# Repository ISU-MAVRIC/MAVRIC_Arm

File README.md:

# MAVRIC_Arm
The MAVRIC Arm consists of a rotating base (stepper motor), 'shoulder' actuator (with feedback), 'elbow' actuator (with feedback), and an end effector. The end effector is modular but at its maximum contains a rotation servo, horizontal servo, vertical servo, and gripping servo. This board interfaces with the MAVRIC main board, receiving control packets and sending back status packets.

**Features**
- 4 7.4V 5A Buck Regulators powering the high power end effector servos
  - Current measurement on every power output to prevent overheating of both the regulators and the servos themselves
- 3V3 and 5V Buck Regulators powering the STM32 and an external Raspberry Pi
- Powered by single 12V battery rail
- STM32 communicating over RS-485 with the MAVRIC main board for control/status transmission
- STM32 generating PWM to control the actuator drivers, servos, and stepper driver

## Arm Board Prototype 1 Ordered:

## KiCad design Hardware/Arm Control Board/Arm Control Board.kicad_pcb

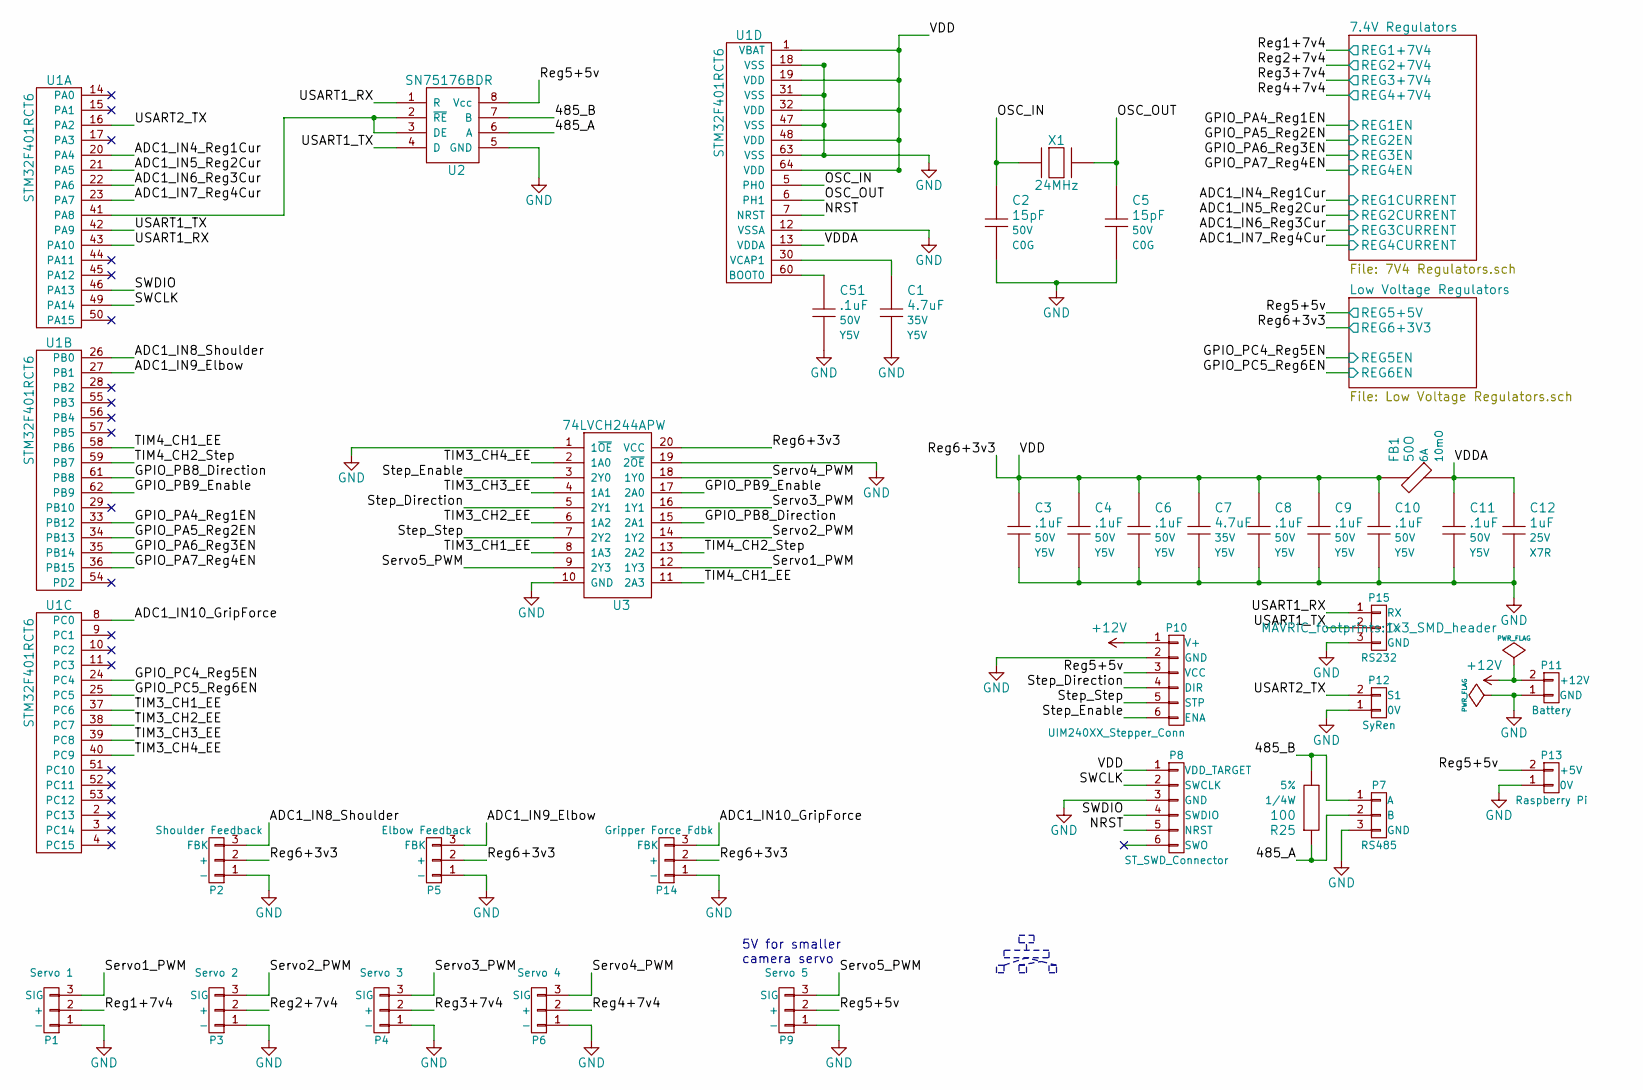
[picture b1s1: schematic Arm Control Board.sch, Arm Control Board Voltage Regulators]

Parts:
C1, C7: 4.7uF; C_1206_HandSoldering; Voltage 35V; Manufacturer Part # GMK316F475ZG-T
C2, C5: 15pF; C_1206_HandSoldering; Voltage 50V; Manufacturer Part # CL31C150JBCNNNC
C3, C4, C6, C8, C9, C10, C11, C51: .1uF; C_1206_HandSoldering; Voltage 50V; Manufacturer Part # CL31F104MBCNNNC
C12: 1uF; C_1206_HandSoldering; Voltage 25V; Manufacturer Part # C1206C105M3RACTU
FB1: 50O; R_1206_HandSoldering; Manufacturer Part # HI1206T500R-10
P1: Servo 1; 1x3_SMD_header
P2: Shoulder Feedback; 1x3_SMD_header
P3: Servo 2; 1x3_SMD_header
P4: Servo 3; 1x3_SMD_header
P5: Elbow Feedback; 1x3_SMD_header
P6: Servo 4; 1x3_SMD_header
P7: RS485; 1x3_SMD_header
P8: ST_SWD_Connector; 1x6_SMD_header
P9: Servo 5; 1x3_SMD_header
P10: UIM240XX_Stepper_Conn; 1x6_SMD_header
P11: Battery; SolderWirePad_2x_2-5mmDrill
P12: SyRen; 1x2_SMD_header
P13: Raspberry Pi; 1x2_SMD_header
P14: Gripper Force Fdbk; 1x3_SMD_header
P15: RS232; 1x3_SMD_header
R25: 100; R_1206_HandSoldering; Tolerance 5%; Manufacturer Part # ERJ-8GEYJ101V
U1: STM32F401RCT6; LQFP-64_10x10mm_Pitch0.5mm
U2: SN75176BDR; SOIC-8-W
U3: 74LVCH244APW; AB2_TSSOP20
X1: 24MHz; Q_49U3HMS; Tolerance 30ppm; Manufacturer Part # 9C-24.000MAAE-T; Digi-Key Value

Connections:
+12V: P10.1 (V+), P11.2 (+12V); also elsewhere on the board
/7.4V Regulators/REG1+7V4: P1.2 (+); also elsewhere on the board
/7.4V Regulators/REG1CURRENT: U1.20 (PA4); also elsewhere on the board
/7.4V Regulators/REG1EN: U1.33 (PB12); also elsewhere on the board
/7.4V Regulators/REG2+7V4: P3.2 (+); also elsewhere on the board
/7.4V Regulators/REG2CURRENT: U1.21 (PA5); also elsewhere on the board
/7.4V Regulators/REG2EN: U1.34 (PB13); also elsewhere on the board
/7.4V Regulators/REG3+7V4: P4.2 (+); also elsewhere on the board
/7.4V Regulators/REG3CURRENT: U1.22 (PA6); also elsewhere on the board
/7.4V Regulators/REG3EN: U1.35 (PB14); also elsewhere on the board
/7.4V Regulators/REG4+7V4: P6.2 (+); also elsewhere on the board
/7.4V Regulators/REG4CURRENT: U1.23 (PA7); also elsewhere on the board
/7.4V Regulators/REG4EN: U1.36 (PB15); also elsewhere on the board
/485_A: P7.2 (B), R25.1, U2.6 (A)
/485_B: P7.1 (A), R25.2, U2.7 (B)
/ADC1_IN8_Shoulder: P2.3 (FBK), U1.26 (PB0)
/ADC1_IN9_Elbow: P5.3 (FBK), U1.27 (PB1)
/ADC1_IN10_GripForce: P14.3 (FBK), U1.8 (PC0)
/GPIO_PB8_Direction: U1.61 (PB8), U3.15 (2A1)
/GPIO_PB9_Enable: U1.62 (PB9), U3.17 (2A0)
/Low Voltage Regulators/REG5+5V: P9.2 (+), P10.3 (VCC), P13.2 (+5V), U2.8 (Vcc); also elsewhere on the board
/Low Voltage Regulators/REG5EN: U1.24 (PC4); also elsewhere on the board
/Low Voltage Regulators/REG6+3V3: C3.1, C4.1, C6.1, C7.1, C8.1, C9.1, C10.1, FB1.1, P2.2 (+), P5.2 (+), P8.1 (VDD_TARGET), P14.2 (+), U1.1 (VBAT), U1.19 (VDD), U1.32 (VDD), U1.48 (VDD), U1.64 (VDD), U3.20 (VCC); also elsewhere on the board
/Low Voltage Regulators/REG6EN: U1.25 (PC5); also elsewhere on the board
/NRST: P8.5 (NRST), U1.7 (NRST)
/OSC_IN: C2.1, U1.5 (PH0), X1.1
/OSC_OUT: C5.1, U1.6 (PH1), X1.2
/SWCLK: P8.2 (SWCLK), U1.49 (PA14)
/SWDIO: P8.4 (SWDIO), U1.46 (PA13)
/Servo1_PWM: P1.3 (SIG), U3.12 (1Y3)
/Servo2_PWM: P3.3 (SIG), U3.14 (1Y2)
/Servo3_PWM: P4.3 (SIG), U3.16 (1Y1)
/Servo4_PWM: P6.3 (SIG), U3.18 (1Y0)
/Servo5_PWM: P9.3 (SIG), U3.9 (2Y3)
/Step_Direction: P10.4 (DIR), U3.5 (2Y1)
/Step_Enable: P10.6 (ENA), U3.3 (2Y0)
/Step_Step: P10.5 (STP), U3.7 (2Y2)
/TIM3_CH1_EE: U1.37 (PC6), U3.8 (1A3)
/TIM3_CH2_EE: U1.38 (PC7), U3.6 (1A2)
/TIM3_CH3_EE: U1.39 (PC8), U3.4 (1A1)
/TIM3_CH4_EE: U1.40 (PC9), U3.2 (1A0)
/TIM4_CH1_EE: U1.58 (PB6), U3.11 (2A3)
/TIM4_CH2_Step: U1.59 (PB7), U3.13 (2A2)
/USART1_RX: P15.1 (RX), U1.43 (PA10), U2.1 (R)
/USART1_TX: P15.2 (TX), U1.42 (PA9), U2.4 (D)
/USART2_TX: P12.2 (S1), U1.16 (PA2)
/VDDA: C11.1, C12.1, FB1.2, U1.13 (VDDA)
GND: C1.2, C2.2, C3.2, C4.2, C5.2, C6.2, C7.2, C8.2, C9.2, C10.2, C11.2, C12.2, C51.2, P1.1 (-), P2.1 (-), P3.1 (-), P4.1 (-), P5.1 (-), P6.1 (-), P7.3 (GND), P8.3 (GND), P9.1 (-), P10.2 (GND), P11.1 (GND), P12.1 (0V), P13.1 (0V), P14.1 (-), P15.3 (GND), U1.12 (VSSA), U1.18 (VSS), U1.31 (VSS), U1.47 (VSS), U1.63 (VSS), U2.5 (GND), U3.1 (1~OE), U3.10 (GND), U3.19 (2~OE); also elsewhere on the board
unnamed: C1.1, U1.30 (VCAP1)
unnamed: C51.1, U1.60 (BOOT0)
unnamed: U1.41 (PA8), U2.2 (~RE), U2.3 (DE)

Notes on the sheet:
5V for smaller camera servo

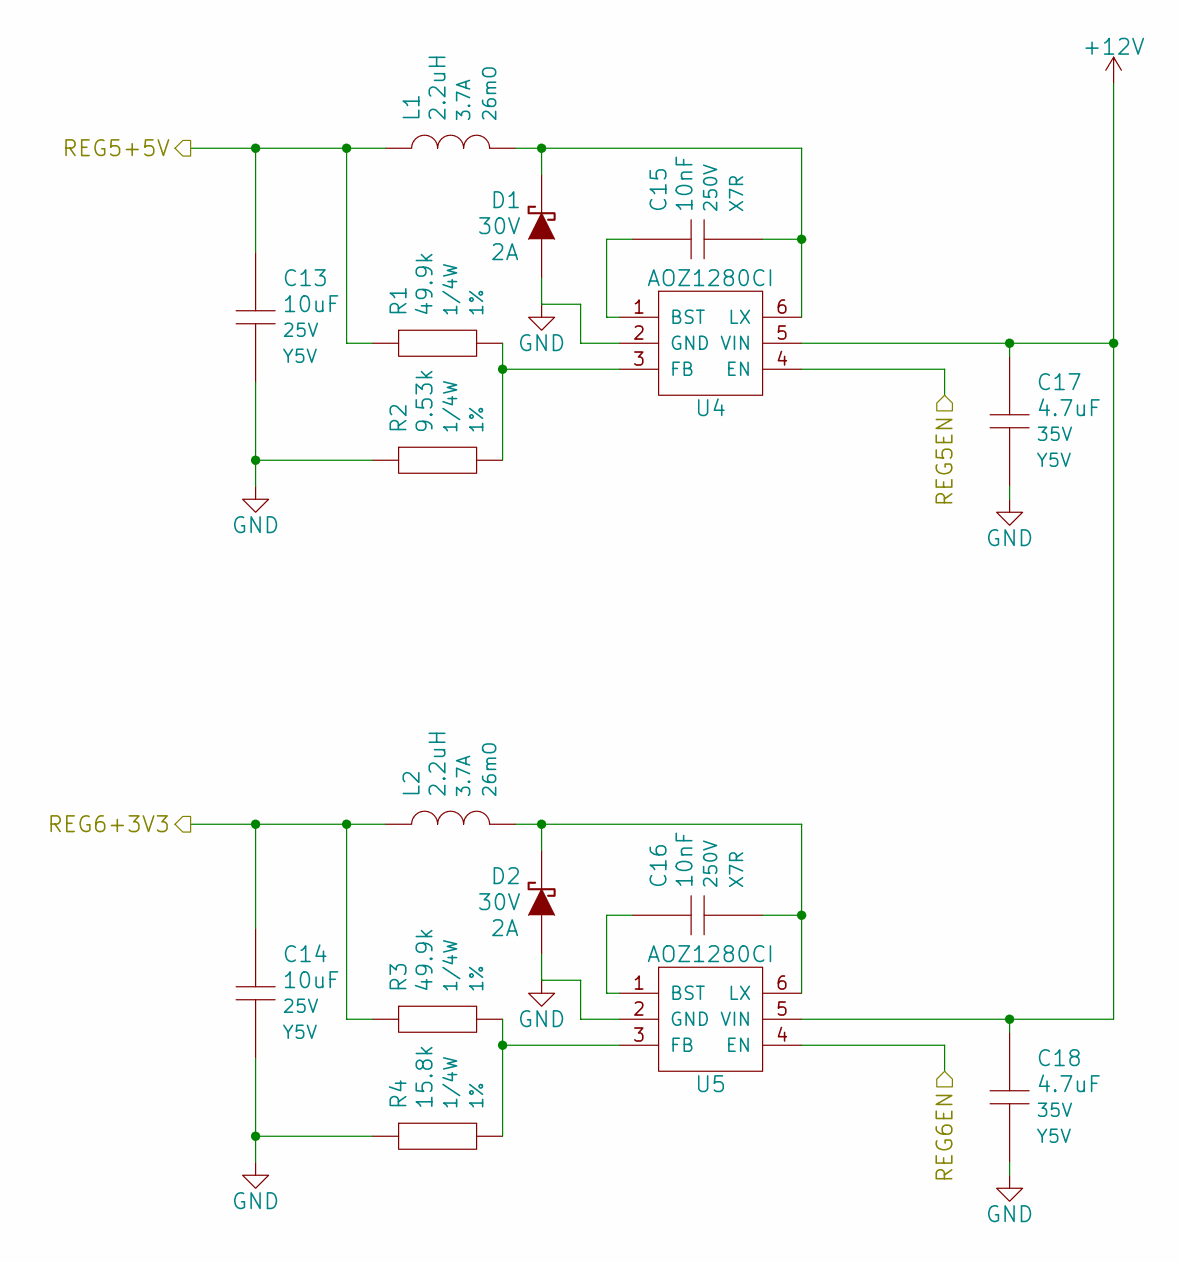
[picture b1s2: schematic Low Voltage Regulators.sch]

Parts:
C13, C14: 10uF; C_1206_HandSoldering; Voltage 25V; Manufacturer Part # TMK316F106ZL-T
C15, C16: 10nF; C_1206_HandSoldering; Voltage 250V; Manufacturer Part # C1206C103JARACTU; Digi-Key Value
C17, C18: 4.7uF; C_1206_HandSoldering; Voltage 35V; Manufacturer Part # GMK316F475ZG-T
D1, D2: DIODESCH; Diode_MicroSMP; Reverse Voltage 30V; Manufacturer Part # MSS2P3-M3/89A
L1, L2: 2.2uH; Yuden_SMD_Power_Inductor_6060; Manufacturer Part # NR6028T2R2N
R1, R3: 49.9k; R_1206_HandSoldering; Tolerance 1%; Manufacturer Part # RC1206FR-0749K9L
R2: 9.53k; R_1206_HandSoldering; Tolerance 1%; Manufacturer Part # RC1206FR-079K53L
R4: 15.8k; R_1206_HandSoldering; Tolerance 1%; Manufacturer Part # RC1206FR-0715K8L
U4, U5: AOZ1280CI; SOT-23-6

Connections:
+12V: C17.1, C18.1, U4.5 (VIN), U5.5 (VIN); also elsewhere on the board
/Low Voltage Regulators/REG5+5V: C13.1, L1.1, R1.1; also elsewhere on the board
/Low Voltage Regulators/REG5EN: U4.4 (EN); also elsewhere on the board
/Low Voltage Regulators/REG6+3V3: C14.1, L2.1, R3.1; also elsewhere on the board
/Low Voltage Regulators/REG6EN: U5.4 (EN); also elsewhere on the board
GND: C13.2, C14.2, C17.2, C18.2, D1.1 (A), D2.1 (A), R2.1, R4.1, U4.2 (GND), U5.2 (GND); also elsewhere on the board
unnamed: C15.1, U4.1 (BST)
unnamed: C15.2, D1.2 (K), L1.2, U4.6 (LX)
unnamed: C16.1, U5.1 (BST)
unnamed: C16.2, D2.2 (K), L2.2, U5.6 (LX)
unnamed: R1.2, R2.2, U4.3 (FB)
unnamed: R3.2, R4.2, U5.3 (FB)

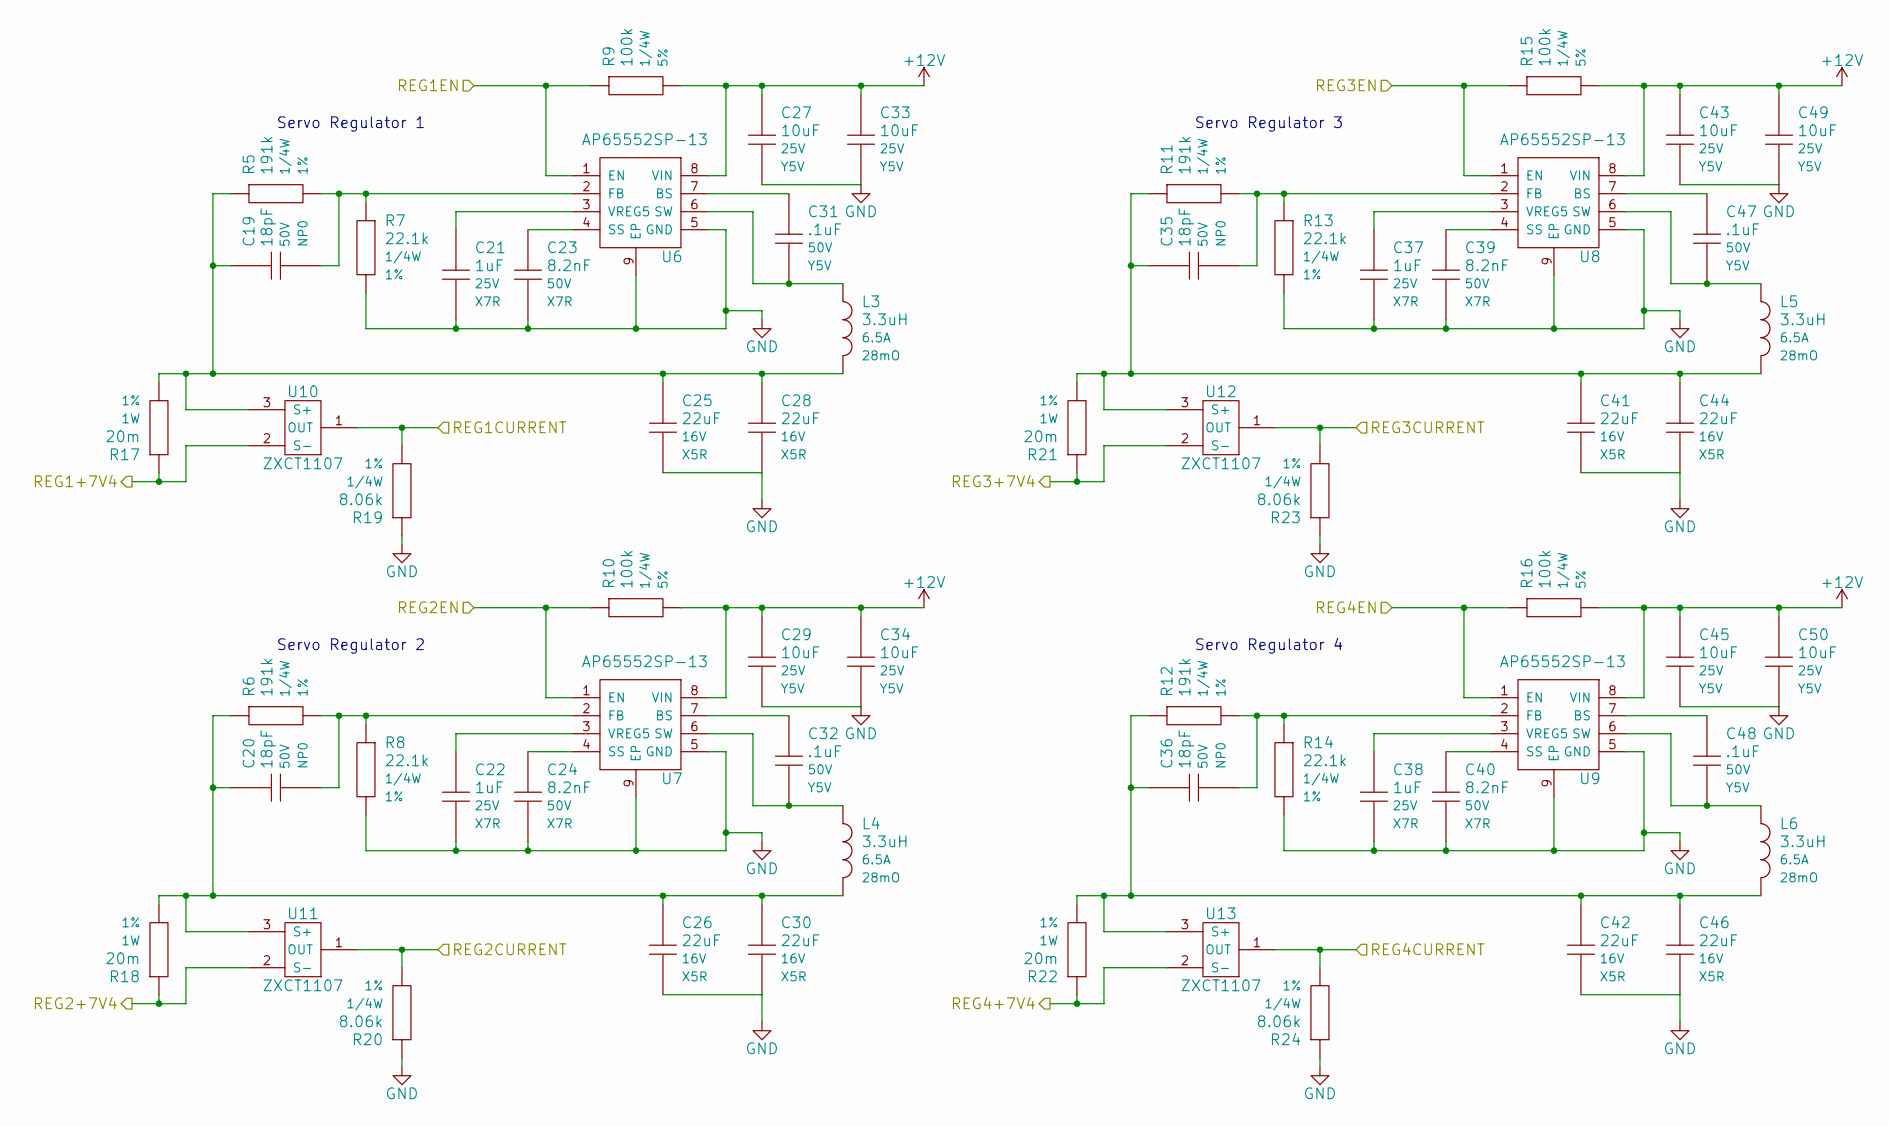
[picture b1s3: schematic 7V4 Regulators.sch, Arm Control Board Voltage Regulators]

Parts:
C19, C20, C35, C36: 18pF; C_1206_HandSoldering; Voltage 50V; Manufacturer Part # CC1206JRNPO9BN180
C21, C22, C37, C38: 1uF; C_1206_HandSoldering; Voltage 25V; Manufacturer Part # C1206C105M3RACTU
C23, C24, C39, C40: 8.2nF; C_1206_HandSoldering; Voltage 50V; Manufacturer Part # CC1206KRX7R9BB822
C25, C26, C28, C30, C41, C42, C44, C46: 22uF; C_1206_HandSoldering; Voltage 16V; Manufacturer Part # CL31A226MOCLNNC
C27, C29, C33, C34, C43, C45, C49, C50: 10uF; C_1206_HandSoldering; Voltage 25V; Manufacturer Part # TMK316F106ZL-T
C31, C32, C47, C48: .1uF; C_1206_HandSoldering; Voltage 50V; Manufacturer Part # CL31F104MBCNNNC
L3, L4, L5, L6: 3.3uH; Neosid_Inductor_SM-PIC0612H; Manufacturer Part # ASPI-0630LR-3R3M-T15
R5, R6, R11, R12: 191k; R_1206_HandSoldering; Tolerance 1%; Manufacturer Part # RC1206FR-07191KL
R7, R8, R13, R14: 22.1k; R_1206_HandSoldering; Tolerance 1%; Manufacturer Part # RC1206FR-0722K1L
R9, R10, R15, R16: 100k; R_1206_HandSoldering; Tolerance 5%; Manufacturer Part # RC1206JR-07100KL
R17, R18, R21, R22: 20m; R_1206_HandSoldering; Tolerance 1%; Manufacturer Part # LRMAM1206-R02FT5
R19, R20, R23, R24: 8.06k; R_1206_HandSoldering; Tolerance 1%; Manufacturer Part # ERJ-8ENF8061V
U6, U7, U8, U9: AP65552SP-13; SOIC-8-N-1EP
U10, U11, U12, U13: ZXCT1107; SOT23_Transistor_Handsoldering_RevB_14Mar2014

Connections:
+12V: C27.1, C29.1, C33.1, C34.1, C43.1, C45.1, C49.1, C50.1, R9.2, R10.2, R15.2, R16.2, U6.8 (VIN), U7.8 (VIN), U8.8 (VIN), U9.8 (VIN); also elsewhere on the board
/7.4V Regulators/REG1+7V4: R17.1, U10.2 (S-); also elsewhere on the board
/7.4V Regulators/REG1CURRENT: R19.2, U10.1 (OUT); also elsewhere on the board
/7.4V Regulators/REG1EN: R9.1, U6.1 (EN); also elsewhere on the board
/7.4V Regulators/REG2+7V4: R18.1, U11.2 (S-); also elsewhere on the board
/7.4V Regulators/REG2CURRENT: R20.2, U11.1 (OUT); also elsewhere on the board
/7.4V Regulators/REG2EN: R10.1, U7.1 (EN); also elsewhere on the board
/7.4V Regulators/REG3+7V4: R21.1, U12.2 (S-); also elsewhere on the board
/7.4V Regulators/REG3CURRENT: R23.2, U12.1 (OUT); also elsewhere on the board
/7.4V Regulators/REG3EN: R15.1, U8.1 (EN); also elsewhere on the board
/7.4V Regulators/REG4+7V4: R22.1, U13.2 (S-); also elsewhere on the board
/7.4V Regulators/REG4CURRENT: R24.2, U13.1 (OUT); also elsewhere on the board
/7.4V Regulators/REG4EN: R16.1, U9.1 (EN); also elsewhere on the board
GND: C21.2, C22.2, C23.2, C24.2, C25.2, C26.2, C27.2, C28.2, C29.2, C30.2, C33.2, C34.2, C37.2, C38.2, C39.2, C40.2, C41.2, C42.2, C43.2, C44.2, C45.2, C46.2, C49.2, C50.2, R7.2, R8.2, R13.2, R14.2, R19.1, R20.1, R23.1, R24.1, U6.5 (GND), U6.9 (EP), U7.5 (GND), U7.9 (EP), U8.5 (GND), U8.9 (EP), U9.5 (GND), U9.9 (EP); also elsewhere on the board
unnamed: C19.1, C25.1, C28.1, L3.2, R5.1, R17.2, U10.3 (S+)
unnamed: C19.2, R5.2, R7.1, U6.2 (FB)
unnamed: C20.1, C26.1, C30.1, L4.2, R6.1, R18.2, U11.3 (S+)
unnamed: C20.2, R6.2, R8.1, U7.2 (FB)
unnamed: C21.1, U6.3 (VREG5)
unnamed: C22.1, U7.3 (VREG5)
unnamed: C23.1, U6.4 (SS)
unnamed: C24.1, U7.4 (SS)
unnamed: C31.1, U6.7 (BS)
unnamed: C31.2, L3.1, U6.6 (SW)
unnamed: C32.1, U7.7 (BS)
unnamed: C32.2, L4.1, U7.6 (SW)
unnamed: C35.1, C41.1, C44.1, L5.2, R11.1, R21.2, U12.3 (S+)
unnamed: C35.2, R11.2, R13.1, U8.2 (FB)
unnamed: C36.1, C42.1, C46.1, L6.2, R12.1, R22.2, U13.3 (S+)
unnamed: C36.2, R12.2, R14.1, U9.2 (FB)
unnamed: C37.1, U8.3 (VREG5)
unnamed: C38.1, U9.3 (VREG5)
unnamed: C39.1, U8.4 (SS)
unnamed: C40.1, U9.4 (SS)
unnamed: C47.1, U8.7 (BS)
unnamed: C47.2, L5.1, U8.6 (SW)
unnamed: C48.1, U9.7 (BS)
unnamed: C48.2, L6.1, U9.6 (SW)

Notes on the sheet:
Servo Regulator 1
Servo Regulator 2
Servo Regulator 3
Servo Regulator 4

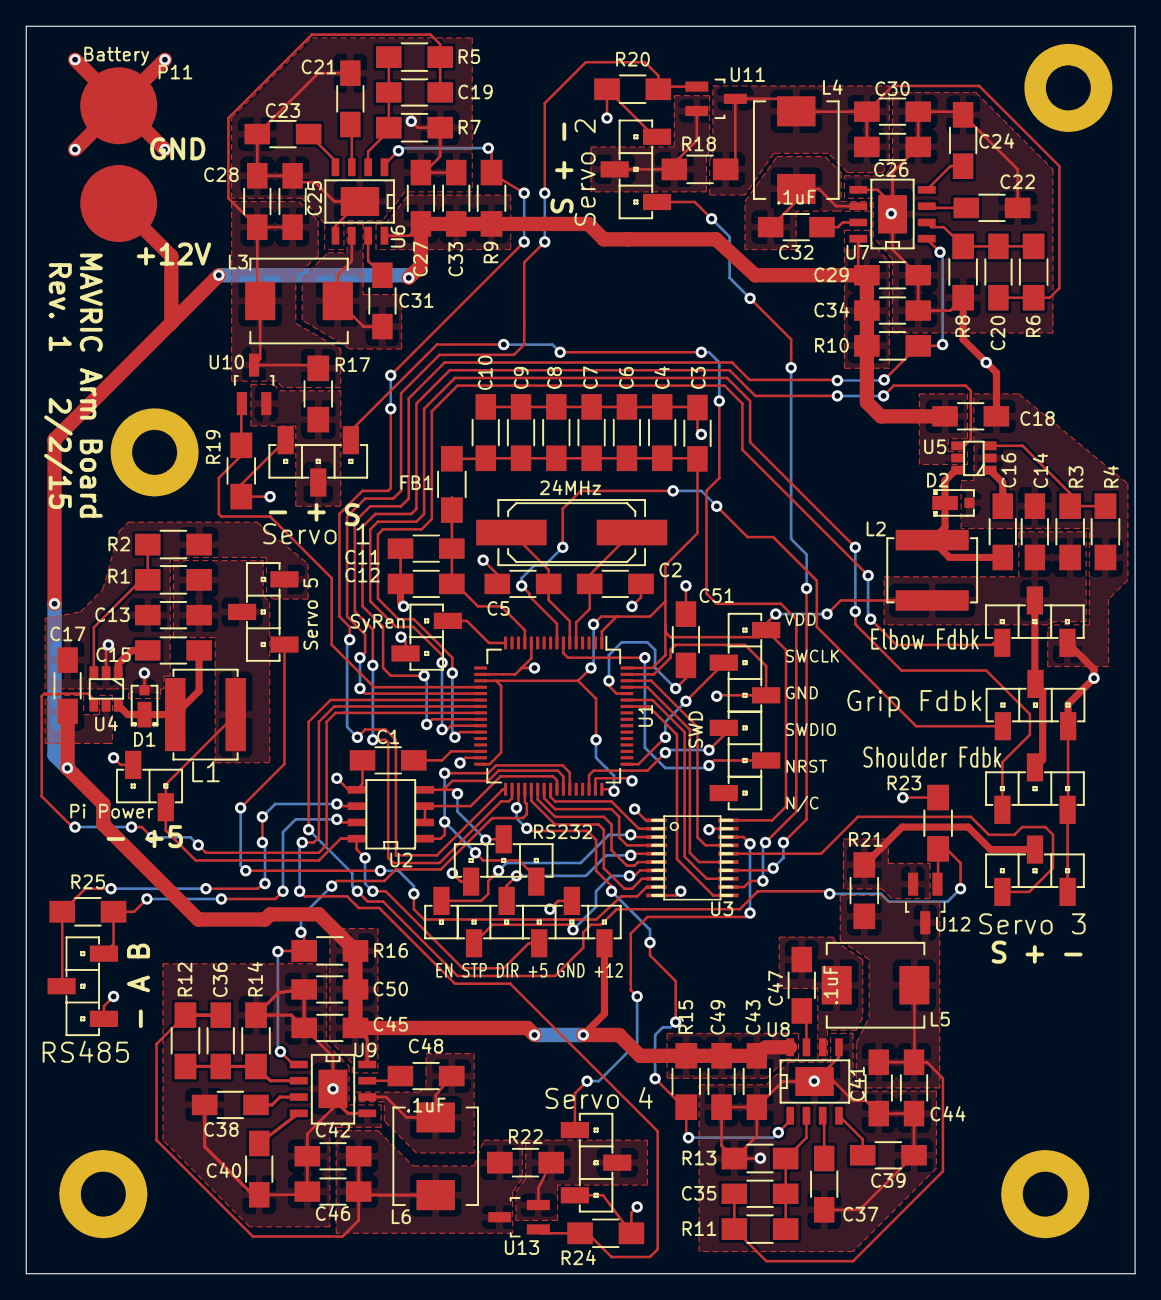
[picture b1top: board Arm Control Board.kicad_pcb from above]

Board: 2 copper layers, 86.4 x 97.2 mm, 118 parts (0 on the bottom side), 81 nets.

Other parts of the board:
MountingHole_3-5mm, MountingHole_3-5mm#2, MountingHole_3-5mm#3, MountingHole_3-5mm#4: VAL**; PlatedMountingHole_3-5mm

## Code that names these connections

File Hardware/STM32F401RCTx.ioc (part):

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Mcu.Name=STM32F401R(B-C-D-E)Tx
Mcu.Package=LQFP64
Mcu.UserName=STM32F401RCTx
PA10.Mode=Asynchronous
PA10.Signal=USART1_RX
PA13.Mode=Serial-Wire
PA13.Signal=SYS_JTMS-SWDIO
PA14.Mode=Serial-Wire
PA14.Signal=SYS_JTCK-SWCLK
PA2.Mode=Asynchronous
PA2.Signal=USART2_TX
PA3.Mode=Asynchronous
PA3.Signal=USART2_RX
PA4.Signal=ADCx_IN4
PA5.Signal=ADCx_IN5
PA6.Signal=ADCx_IN6
PA7.Signal=ADCx_IN7
PA8.Signal=GPIO_Output
PA9.Mode=Asynchronous
PA9.Signal=USART1_TX
PB0.Signal=ADCx_IN8
PB1.Signal=ADCx_IN9
PB12.Signal=GPIO_Output
PB13.Signal=GPIO_Output
PB14.Signal=GPIO_Output
PB15.Signal=GPIO_Output
PB6.Signal=S_TIM4_CH1
PB7.Signal=S_TIM4_CH2
PB8.Signal=GPIO_Output
PB9.Signal=GPIO_Output
PC0.Signal=ADCx_IN10
PC4.Signal=GPIO_Output
PC5.Signal=GPIO_Output
PC6.Signal=S_TIM3_CH1
PC7.Signal=S_TIM3_CH2
PC8.Signal=S_TIM3_CH3
PC9.Signal=S_TIM3_CH4
PH0\ -\ OSC_IN.Signal=RCC_OSC_IN
PH1\ -\ OSC_OUT.Signal=RCC_OSC_OUT
RCC.HSE_VALUE=25000000
RCC.SYSCLKFreq_VALUE=16000000

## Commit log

2015-01-25 Blank project files added
2015-01-25 Created STM32CubeMX Project
2015-01-25 Added regulator to schematic
    Also added gitignore, parts list, and microcontroller datasheet
2015-01-25 Added datasheets
2015-01-26 Added new AP65552SP-13 regulator circuit
    More current for the servos
2015-01-26 Creating servo regulator circuits, datasheets
2015-01-26 Added enable pins to all servo regulators
    Might not need them all independent, we'll see
2015-01-26 Added and connected servo plugs
2015-01-26 Added lower cost 485 Transceiver, connected serial
2015-01-26 Added whiteboard layout from 1/24/15
2015-01-26 Added SyRen serial connector
2015-01-26 Raspberry Pi power connector + started STM32 power
2015-01-28 Added .db files to .gitignore because windows
2015-01-28 Added 74LVCH244APW buffer to servo lines
    Able to push much more current than the micro can
2015-01-28 Attempt to ignore $ files from KiCad
2015-01-28 Attempt 2 to ignore $ files
2015-01-28 Cleaned up schematic, cube, added stepper connector
2015-01-28 More clean up, added connector for actuator fbck
2015-01-28 Added SWD connector for program/debug
2015-01-28 Fixed some floating wires
2015-01-29 Reorganized regulators, added 5V reg, ext osc, PNs
    Way too much for one commit, sorry about that. Reorganized the
    regulators into high voltage/low voltage sheets. Added product numbers
    to all passives + more. Check issues for any other changes
2015-01-29 More footprints added, components annotated
2015-01-29 Initial PCB layout
2015-01-30 all components have footprints assigned now
2015-01-30 Fixed pin numbers being names
    Crime doesn't pay, kids. If your names aren't showing up on your part,
    don't just make the numbers your names. Find out how to make the names
    show up.
2015-01-30 Fixed parts with pin numbers starting at zero
    just a zero indexed man living in a one indexed world
2015-01-30 reg1 layout made
    expecting it to change bunches
2015-01-30 started reg2 layout
2015-01-31 Attached BOOT0 and VBAT
2015-01-31 created a couple of different 7v4 regulator layouts
2015-01-31 honestly I have no clue but kicad wanted to save
    sorry guys really dropped the ball on this commit
2015-02-01 reg4 converted to datasheet recommended layout
    it's kind of crazy i didn't think to look there first before I created
    three of my own
2015-02-01 adding vias so the ground doesn't com*plane*
2015-02-02 more vias but to be honest the situation is a mess
2015-02-07 Added current sensing to reg1-4, updated STMCube
    Only high current servo outputs have current sensing. STMCube was not up
    to date with pin assignments. Issues: #18 #15
2015-02-08 Fixed STM32 Part
    Had extra two VSS + VDD pins that didn't exist. Added PD2 pin. Resolves
    #19
2015-02-08 Fixed power connections to STM32
    The part changes screwed some connections up
2015-02-08 Added clamp force sensor port in cube and schematic
    Resolves #20
2015-02-08 Lay out regulators 1-4, update cube for oscillator
    Got strangely excited about this commit. Almost called my dad...
2015-02-09 Initial layout of Regulator 5 (AOZ)
    Followed datasheet recommendations pretty well, probably some room for
    improvement
2015-02-09 Initial layout of Reg 6 (AOZ) and reorg of reg1-4
2015-02-09 Continuation of board layout. 80% connected
    Very poor layout so far, this will change drastically before fab
2015-02-09 Reorganize all regulators. Reorganize buffer pins
    Pins reorganized to simplify board flow
2015-02-09 Connecting more things in better ways
    Just in case i screw something up
2015-02-09 Delete Arm Control Board.kicad_pcb-bak
    Because backups have no place in our repo
2015-02-09 Connect everything but 12V and GND
    Not like those lines are really necessary. MAVRIC is more than capable
    of running off of team spirit, optimism, and enthusiasm.
2015-02-09 Condensing Stage 1
    Just an intermediate commit in case something goes horribly wrong
2015-02-09 Condensing Stage 2
    Still in progress, many of the traces are now in reasonable, space
    conservative spots
2015-02-10 Condensing Stage 3 + Board Outline
2015-02-10 Complete Layout Revision 1
2015-02-10 Fix board outline and export gerbers
2015-02-18 Add terminating resistance for 485, add 232 header
    Resolves #23 #22
2015-02-18 Add value for terminating resistance on 485
    #24
2015-02-19 Improved serial and servo connectors, moved refs
2015-03-03 Reorganize silkscreen
2015-03-03 Add M3 mounting holes
2015-03-03 Plate M3 holes
2015-03-03 Remove back solder mask from plated holes
2015-03-03 Remove front solder mask from plated holes
2015-03-03 Add pinout silk screen text. Exports sent to fab
2015-03-03 Add some pretty board images
2015-03-05 Assemble BOM for initial order
2015-03-28 Add cat5 jack for ethernet
